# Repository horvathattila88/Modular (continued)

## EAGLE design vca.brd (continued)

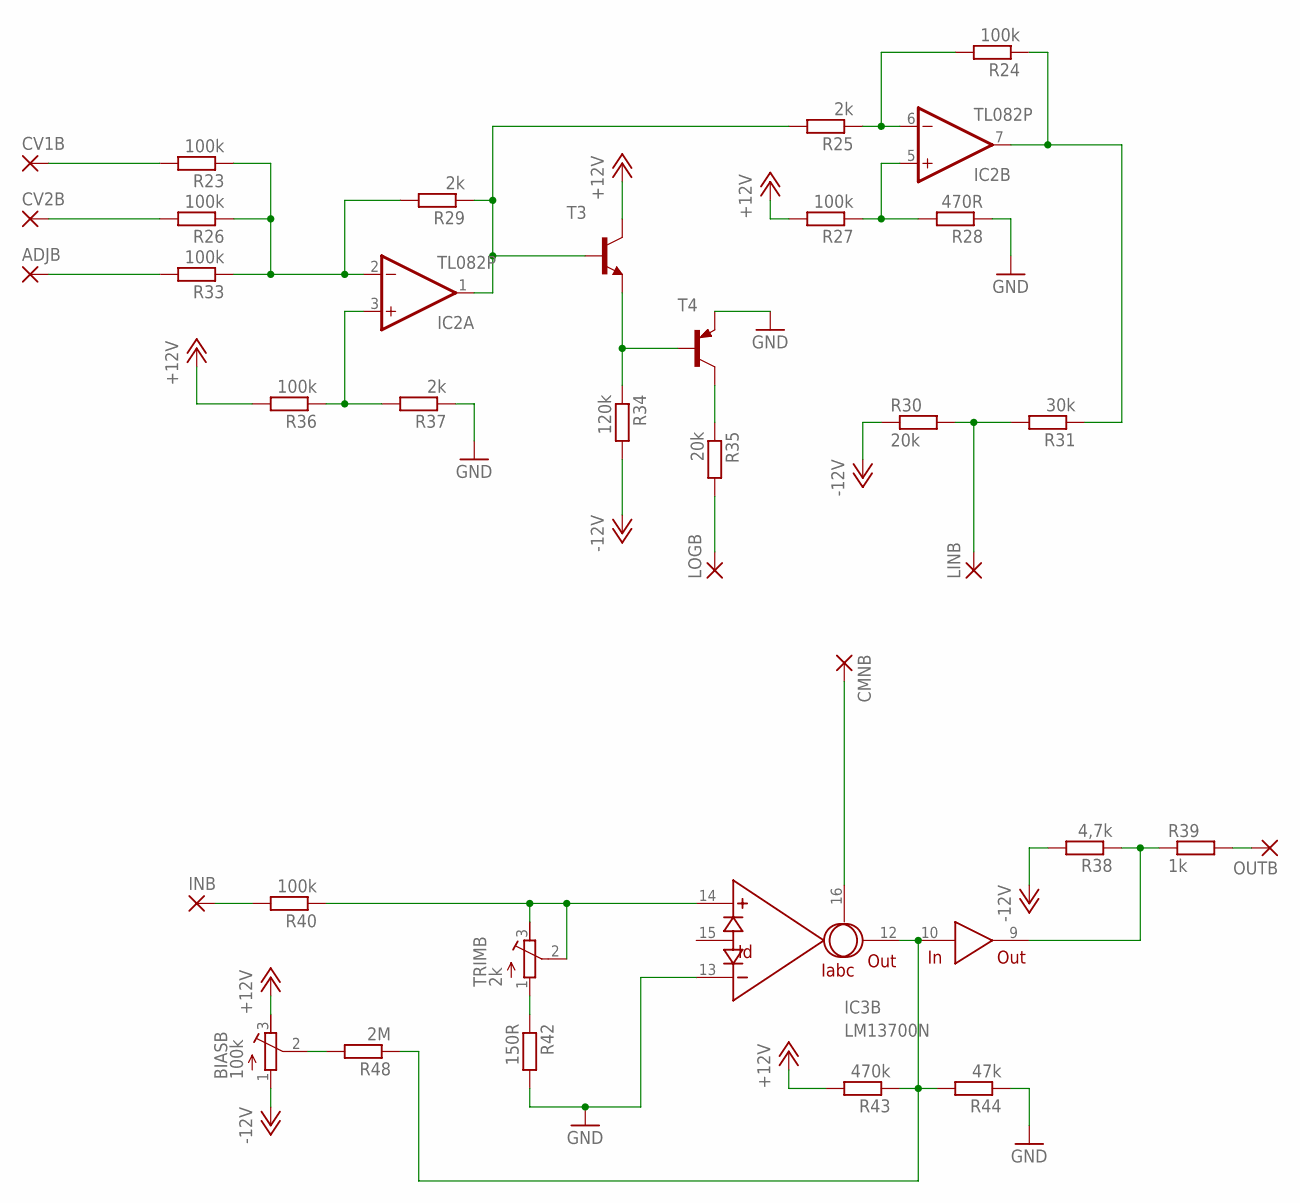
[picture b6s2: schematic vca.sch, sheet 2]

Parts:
ADJB: 2,54/1,0
BIASB: 100k; RTRIM64W
CMNB: 2,54/1,0
CV1B, CV2B: 2,54/1,0
IC2: TL082P; DIL08
IC3: LM13700N; DIL16
INB: 2,54/1,0
LINB: 2,54/1,0
LOGB: 2,54/1,0
OUTB: 2,54/1,0
R23, R26, R33, R40: 100k; 0309V
R24, R27, R36: 100k; 0309/10
R25, R29, R37: 2k; 0309/10
R28: 470R; 0309/10
R30: 20k; 0309V
R31: 30k; 0309V
R34: 120k; 0309/10
R35: 20k; 0309/10
R38: 4,7k; 0309/10
R39: 1k; 0309V
R42: 150R; 0309/10
R43: 470k; 0309/10
R44: 47k; 0309/10
R48: 2M; 0309/10
T3: 2N3904-NPN-TO92-EBC; TO92-EBC
T4: 2N3906-PNP-TO92-EBC; TO92-EBC
TRIMB: 2k; RTRIM64W

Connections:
+12V: BIASB.3 (E), R27.2, R36.2, R43.2, T3.C; also elsewhere on the board
-12V: BIASB.1 (A), R30.1, R34.2, R38.2; also elsewhere on the board
GND: IC3.13 (-IN), R28.1, R37.1, R42.2, R44.1, T4.E; also elsewhere on the board
unnamed: CV1B.1, R23.2
unnamed: CV2B.1, R26.2
unnamed: ADJB.1, R33.2
unnamed: IC2.2 (-IN), R23.1, R26.1, R29.2, R33.1
unnamed: IC2.3 (+IN), R36.1, R37.2
unnamed: IC2.1 (OUT), R25.2, R29.1, T3.B
unnamed: R34.1, T3.E, T4.B
unnamed: R35.1, T4.C
unnamed: LOGB.1, R35.2
unnamed: IC2.6 (-IN), R24.2, R25.1
unnamed: IC2.7 (OUT), R24.1, R31.1
unnamed: IC2.5 (+IN), R27.1, R28.2
unnamed: LINB.1, R30.2, R31.2
unnamed: IC3.10 (IN), IC3.12 (OUT), R43.1, R44.2, R48.1
unnamed: INB.1, R40.2
unnamed: CMNB.1, IC3.16 (IABC)
unnamed: IC3.14 (+IN), R40.1, TRIMB.2 (S), TRIMB.3 (E)
unnamed: R42.1, TRIMB.1 (A)
unnamed: BIASB.2 (S), R48.2
unnamed: OUTB.1, R39.2
unnamed: IC3.9 (OUT), R38.1, R39.1

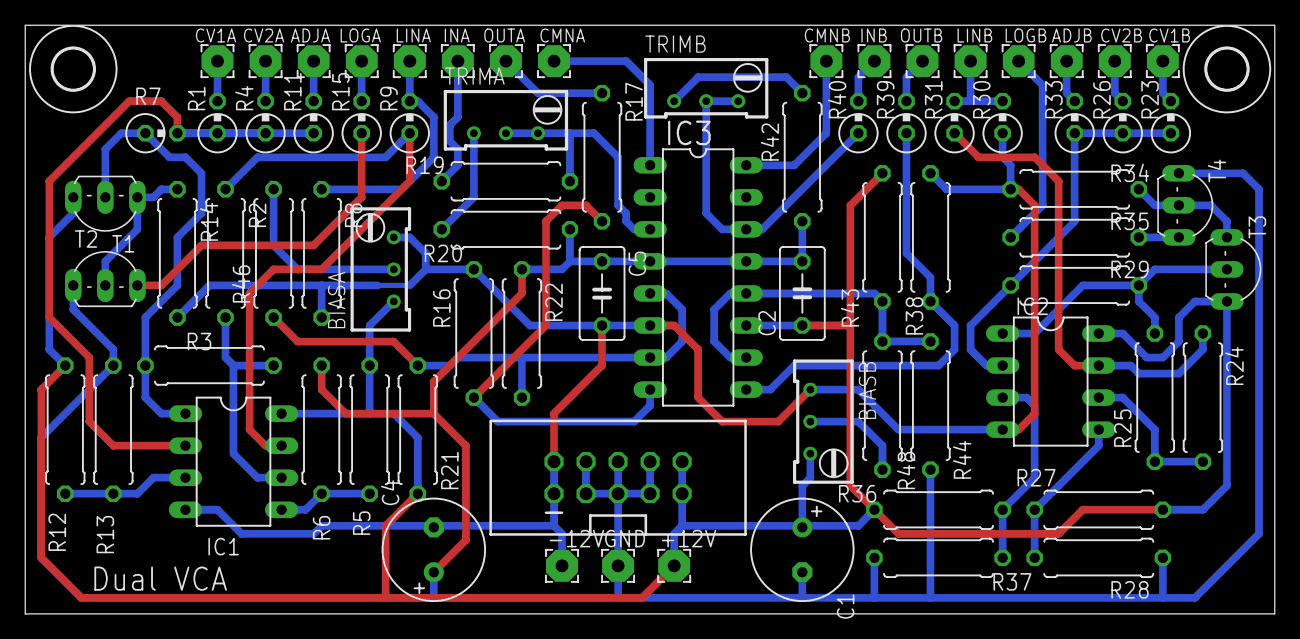
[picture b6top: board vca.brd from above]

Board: 2 copper layers, 99.0 x 46.7 mm, 79 parts (0 on the bottom side), 45 nets.

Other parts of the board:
U$1, U$2: 3,2

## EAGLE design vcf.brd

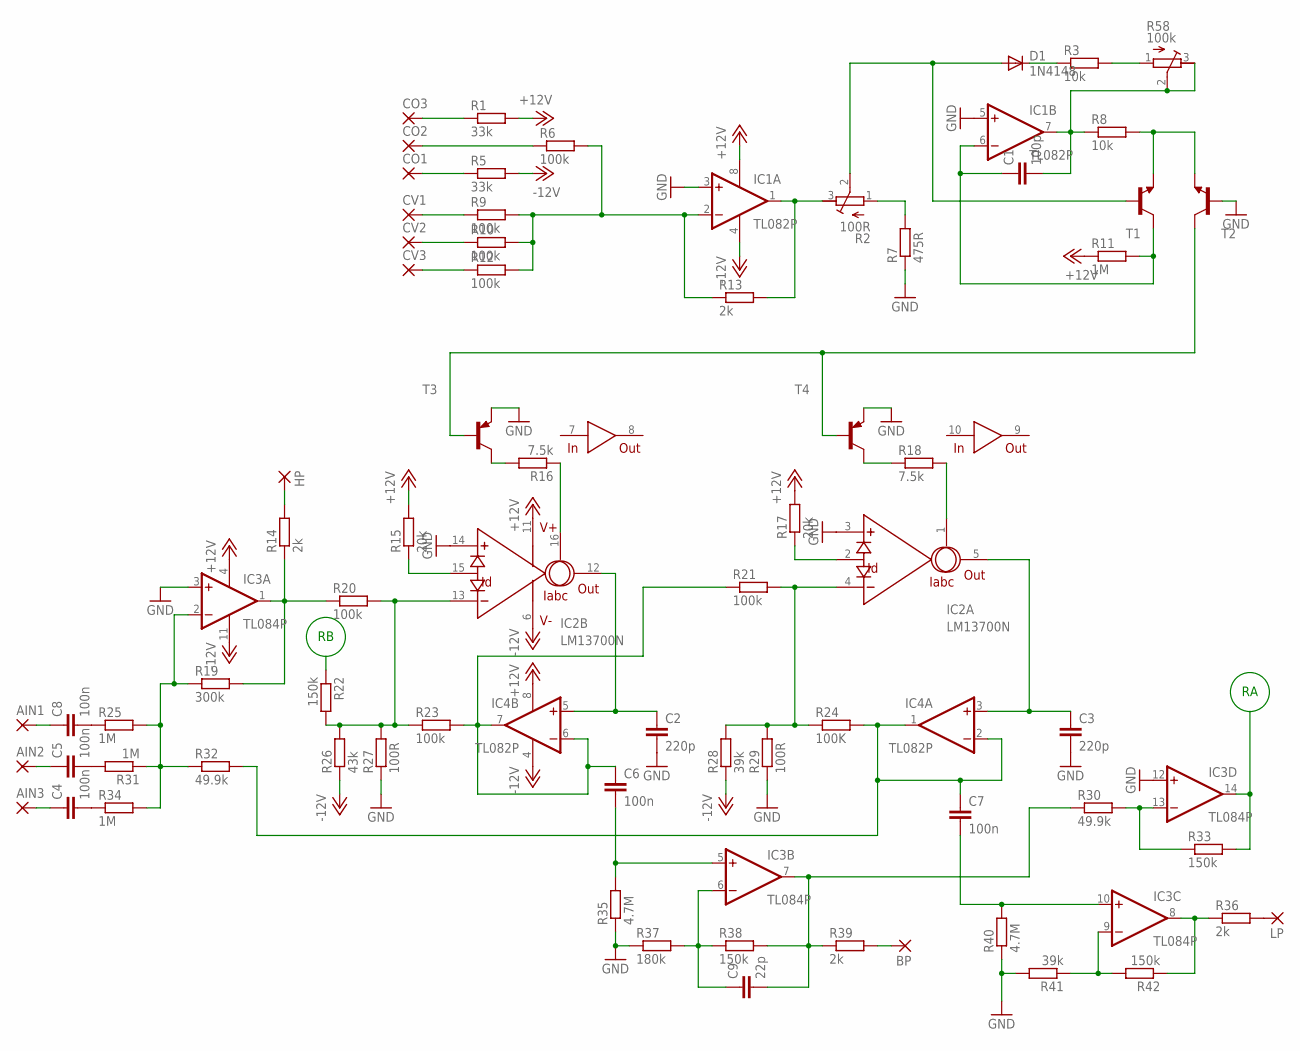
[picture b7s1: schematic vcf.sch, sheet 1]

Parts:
AIN1, AIN2, AIN3: 2,54/1,0
BP: 2,54/1,0
C1: 100p; C050-035X075
C2, C3: 220p; C050-035X075
C4, C5, C6, C7, C8: 100n; C050-035X075
C9: 22p; C050-035X075
CO1, CO2, CO3: 2,54/1,0
CV1, CV2, CV3: 2,54/1,0
D1: 1N4148; DO35-7
HP: 2,54/1,0
IC1, IC4: TL082P; DIL08
IC2: LM13700N; DIL16
IC3: TL084P; DIL14
LP: 2,54/1,0
R1, R5: 33k; 0309V
R2: 100R; RTRIM64W
R3: 10k; 0309V
R6, R9, R10, R12, R20: 100k; 0309V
R7: 475R; 0309V
R8: 10k; 0309/10
R11: 1M; 0309/10
R13, R14: 2k; 0309V
R15, R17: 20k; 0309/10
R16, R18: 7.5k; 0309/10
R19: 300k; 0309V
R21, R23: 100k; 0309/10
R22, R33, R38, R42: 150k; 0309/10
R24: 100K; 0309/10
R25, R31, R34: 1M; 0309V
R26: 43k; 0309V
R27: 100R; 0309V
R28, R41: 39k; 0309/10
R29: 100R; 0309/10
R30: 49.9k; 0309V
R32: 49.9k; 0309/10
R35: 4.7M; 0309V
R36, R39: 2k; 0309/10
R37: 180k; 0309V
R40: 4.7M; 0309/10
R58: 100k; RTRIM64W
T1, T2: 2N3904-NPN-TO92-EBC; TO92-EBC
T3, T4: 2N3906-PNP-TO92-EBC; TO92-EBC

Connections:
+12V: IC1.8 (V+), IC2.11 (V+), IC3.4 (V+), IC4.8 (V+), R1.2, R11.1, R15.2, R17.2; also elsewhere on the board
-12V: IC1.4 (V-), IC2.6 (V-), IC3.11 (V-), IC4.4 (V-), R5.2, R26.1, R28.1; also elsewhere on the board
GND: C2.2, C3.2, IC1.3 (+IN), IC1.5 (+IN), IC2.3 (+IN), IC2.14 (+IN), IC3.3 (+IN), IC3.12 (+IN), R7.1, R27.1, R29.1, R35.1, R37.1, R40.1, R41.2, T2.B, T3.E, T4.E; also elsewhere on the board
unnamed: CO3.1, R1.1
unnamed: CO2.1, R6.1
unnamed: CO1.1, R5.1
unnamed: CV1.1, R9.1
unnamed: CV2.1, R10.1
unnamed: CV3.1, R12.1
unnamed: IC1.2 (-IN), R6.2, R9.2, R10.2, R12.2, R13.1
unnamed: IC1.1 (OUT), R2.3 (E), R13.2
unnamed: R2.1 (A), R7.2
unnamed: C8.2, R25.1
unnamed: R8.2, T1.E, T2.E
unnamed: C1.1, IC1.6 (-IN), R11.2, T1.C
unnamed: D1.C, R3.1
unnamed: R3.2, R58.1 (A)
unnamed: C1.2, IC1.7 (OUT), R8.1, R58.2 (S), R58.3 (E)
unnamed: D1.A, R2.2 (S), T1.B
unnamed: T2.C, T3.B, T4.B
unnamed: C6.2, IC3.5 (+IN), R35.2
unnamed: C5.2, R31.2
unnamed: C4.2, R34.1
unnamed: IC3.1 (OUT), R14.1, R19.2, R20.1
unnamed: HP.1, R14.2
unnamed: IC3.2 (-IN), R19.1, R25.2, R31.1, R32.1, R34.2
unnamed: IC2.13 (-IN), R20.2, R22.2, R23.1, R26.2, R27.2
unnamed: IC2.15 (ID), R15.1
unnamed: IC2.2 (ID), R17.1
unnamed: IC2.16 (IABC), R16.1
unnamed: R16.2, T3.C
unnamed: R18.1, T4.C
unnamed: IC2.1 (IABC), R18.2
unnamed: IC2.4 (-IN), R21.2, R24.1, R28.2, R29.2
unnamed: C6.1, IC4.6 (-IN), IC4.7 (OUT), R21.1, R23.2
unnamed: C2.1, IC2.12 (OUT), IC4.5 (+IN)
unnamed: C3.1, IC2.5 (OUT), IC4.3 (+IN)
unnamed: AIN1.1, C8.1
unnamed: C9.1, IC3.6 (-IN), R37.2, R38.1
unnamed: C9.2, IC3.7 (OUT), R30.1, R38.2, R39.1
unnamed: BP.1, R39.2
unnamed: IC3.13 (-IN), R30.2, R33.1
unnamed: AIN2.1, C5.1
unnamed: C7.2, IC3.10 (+IN), R40.2
unnamed: IC3.9 (-IN), R41.1, R42.2
unnamed: IC3.8 (OUT), R36.1, R42.1
unnamed: LP.1, R36.2
unnamed: AIN3.1, C4.1
unnamed: C7.1, IC4.1 (OUT), IC4.2 (-IN), R24.2, R32.2
RA: IC3.14 (OUT), R33.2; also elsewhere on the board
RB: R22.1; also elsewhere on the board

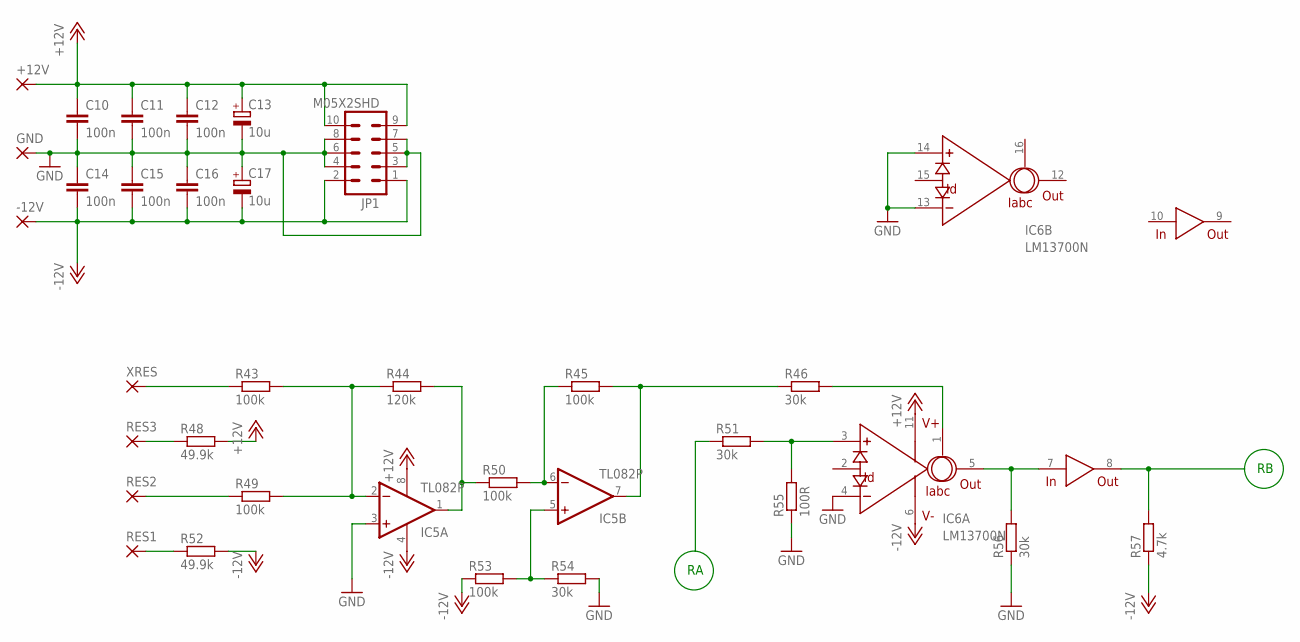
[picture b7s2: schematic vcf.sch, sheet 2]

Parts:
+12V: 2,54/1,0
-12V: 2,54/1,0
C10, C11, C12, C14, C15, C16: 100n; C050-035X075
C13, C17: 10u; E3,5-8
GND: 2,54/1,0
IC5: TL082P; DIL08
IC6: LM13700N; DIL16
JP1: M05X2SHD; 2X5-SHROUDED
R43, R45, R49, R50, R53: 100k; 0309/10
R44: 120k; 0309/10
R46, R51, R54, R56: 30k; 0309/10
R48, R52: 49.9k; 0309/10
R55: 100R; 0309/10
R57: 4.7k; 0309/10
RES1, RES2, RES3: 2,54/1,0
XRES: 2,54/1,0

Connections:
+12V: +12V.1, C10.1, C11.1, C12.1, C13.+, IC5.8 (V+), IC6.11 (V+), JP1.9, JP1.10, R48.2; also elsewhere on the board
-12V: -12V.1, C14.2, C15.2, C16.2, C17.-, IC5.4 (V-), IC6.6 (V-), JP1.1, JP1.2, R52.2, R53.1, R57.1; also elsewhere on the board
GND: C10.2, C11.2, C12.2, C13.-, C14.1, C15.1, C16.1, C17.+, GND.1, IC5.3 (+IN), IC6.4 (-IN), IC6.13 (-IN), IC6.14 (+IN), JP1.3, JP1.4, JP1.5, JP1.6, JP1.7, JP1.8, R54.2, R55.1, R56.1; also elsewhere on the board
unnamed: R43.1, XRES.1
unnamed: R48.1, RES3.1
unnamed: R52.1, RES1.1
unnamed: R49.1, RES2.1
unnamed: IC5.2 (-IN), R43.2, R44.1, R49.2
unnamed: IC5.1 (OUT), R44.2, R50.1
unnamed: IC5.6 (-IN), R45.1, R50.2
unnamed: IC5.5 (+IN), R53.2, R54.1
unnamed: IC6.1 (IABC), R46.2
unnamed: IC5.7 (OUT), R45.2, R46.1
unnamed: IC6.3 (+IN), R51.2, R55.2
unnamed: IC6.5 (OUT), IC6.7 (IN), R56.2
RA: R51.1; also elsewhere on the board
RB: IC6.8 (OUT), R57.2; also elsewhere on the board

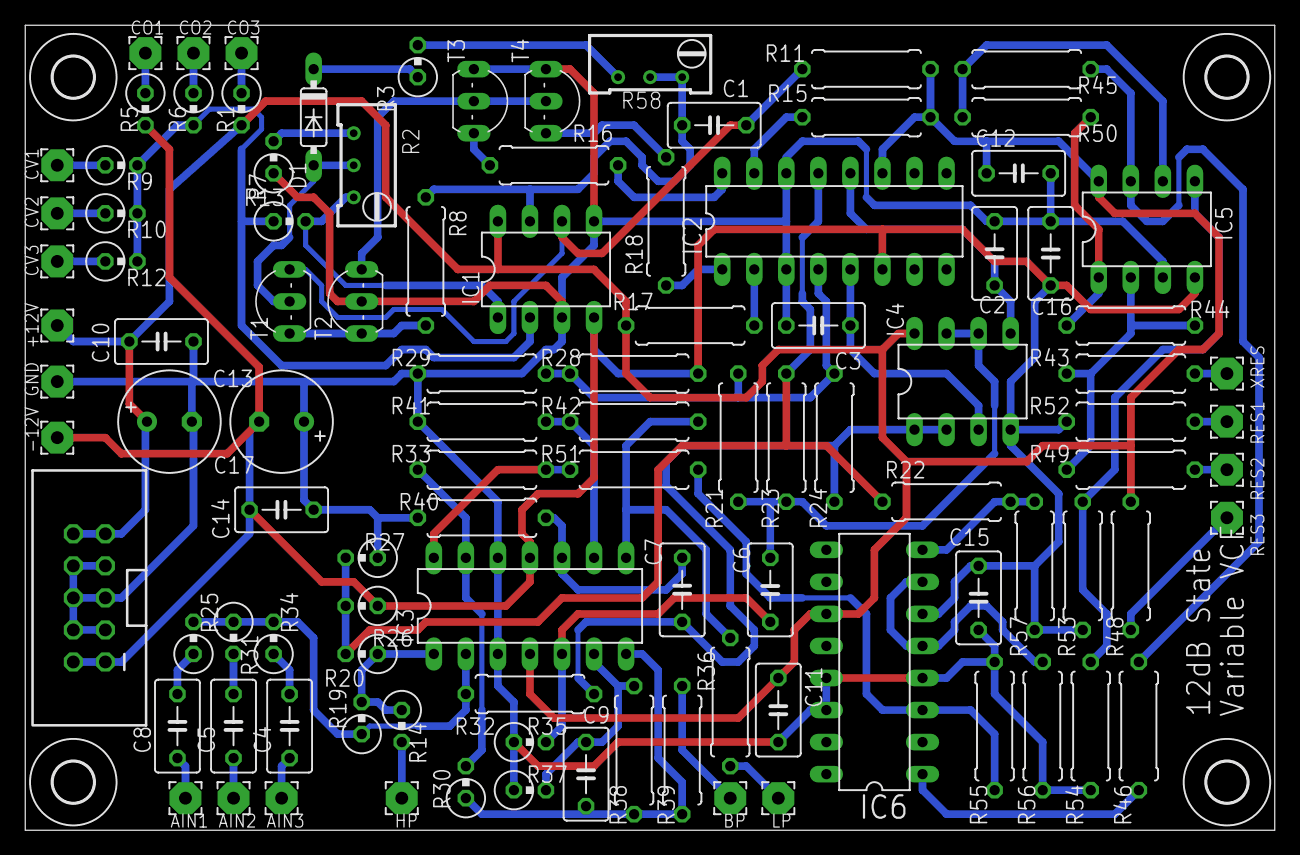
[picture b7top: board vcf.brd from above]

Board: 2 copper layers, 99.0 x 63.8 mm, 108 parts (0 on the bottom side), 63 nets.

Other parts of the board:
U$1, U$2, U$3, U$4: 3,2

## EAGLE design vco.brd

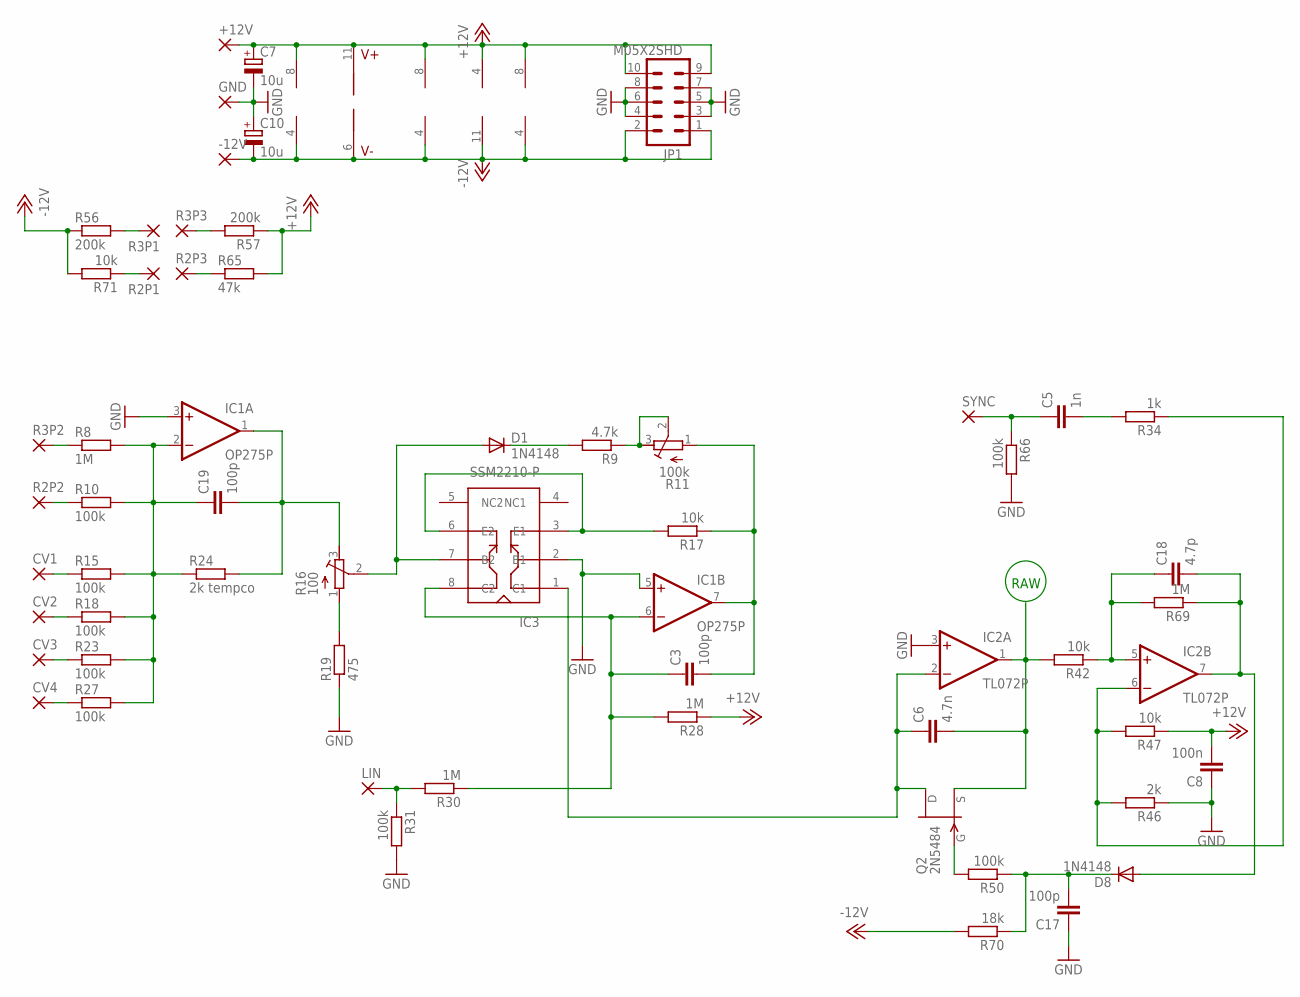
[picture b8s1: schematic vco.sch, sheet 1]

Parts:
+12V: 2,54/1,0
-12V: 2,54/1,0
C3, C17, C19: 100p; C050-045X075
C5: 1n; C050-045X075
C6: 4.7n; C050-045X075
C7, C10: 10u; E2,5-7
C8: 100n; C050-045X075
C18: 4.7p; C050-045X075
CV1, CV2, CV3, CV4: 2,54/1,0
D1, D8: 1N4148; DO35-7
GND: 2,54/1,0
IC1: OP275P; DIL08
IC2, IC6: TL072P; DIL08
IC3: SSM2210-P; DIL08
IC4: TL074P; DIL14
IC5: LM13700N; DIL16
JP1: M05X2SHD; 2X5-SHROUDED
LIN: 2,54/1,0
Q2: 2N5484; TO92-
R2P1, R2P2, R2P3, R3P1, R3P2, R3P3: 2,54/1,0
R8, R28, R30, R69: 1M; 0309V
R9: 4.7k; 0309V
R10, R15, R18, R23, R27, R31, R50, R66: 100k; 0309V
R11: 100k; RTRIM64W
R16: 100; RTRIM64W
R17, R42, R47, R71: 10k; 0309V
R19: 475; 0309V
R24: 2k tempco; 0309/12
R34: 1k; 0309V
R46: 2k; 0309V
R56, R57: 200k; 0309V
R65: 47k; 0309V
R70: 18k; 0309V
SYNC: 2,54/1,0

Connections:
+12V: +12V.1, C7.+, C8.2, IC1.8 (V+), IC2.8 (V+), IC4.4 (V+), IC5.11 (V+), IC6.8 (V+), JP1.9, JP1.10, R28.1, R47.1, R57.1, R65.2; also elsewhere on the board
-12V: -12V.1, C10.-, IC1.4 (V-), IC2.4 (V-), IC4.11 (V-), IC5.6 (V-), IC6.4 (V-), JP1.1, JP1.2, R56.1, R70.2, R71.2; also elsewhere on the board
GND: C7.-, C8.1, C10.+, C17.1, GND.1, IC1.3 (+IN), IC1.5 (+IN), IC2.3 (+IN), IC3.2 (B1), JP1.3, JP1.4, JP1.5, JP1.6, JP1.7, JP1.8, R19.1, R31.2, R46.1, R66.2; also elsewhere on the board
unnamed: R3P1.1, R56.2
unnamed: R2P1.1, R71.1
unnamed: R2P3.1, R65.1
unnamed: R3P3.1, R57.2
unnamed: R3P2.1, R8.1
unnamed: R2P2.1, R10.1
unnamed: CV1.1, R15.1
unnamed: CV2.1, R18.1
unnamed: CV3.1, R23.1
unnamed: CV4.1, R27.1
unnamed: C19.1, IC1.2 (-IN), R8.2, R10.2, R15.2, R18.2, R23.2, R24.1, R27.2
unnamed: C19.2, IC1.1 (OUT), R16.3 (E), R24.2
unnamed: Q2.1 (G), R50.2
unnamed: R16.1 (A), R19.2
unnamed: LIN.1, R30.2, R31.1
unnamed: C3.1, IC1.6 (-IN), IC3.8 (C2), R28.2, R30.1
unnamed: C3.2, IC1.7 (OUT), R11.1 (A), R17.1
unnamed: IC3.3 (E1), IC3.6 (E2), R17.2
unnamed: C17.2, D8.C, R50.1, R70.1
unnamed: C6.1, IC2.2 (-IN), IC3.1 (C1), Q2.3 (D)
unnamed: D1.A, IC3.7 (B2), R16.2 (S)
unnamed: D1.C, R9.2
unnamed: R9.1, R11.2 (S), R11.3 (E)
unnamed: C18.1, IC2.5 (+IN), R42.1, R69.2
unnamed: C18.2, D8.A, IC2.7 (OUT), R69.1
unnamed: IC2.6 (-IN), R34.1, R46.2, R47.2
unnamed: C5.2, R34.2
unnamed: C5.1, R66.1, SYNC.1
RAW: C6.2, IC2.1 (OUT), Q2.2 (S), R42.2; also elsewhere on the board

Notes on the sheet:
RAW

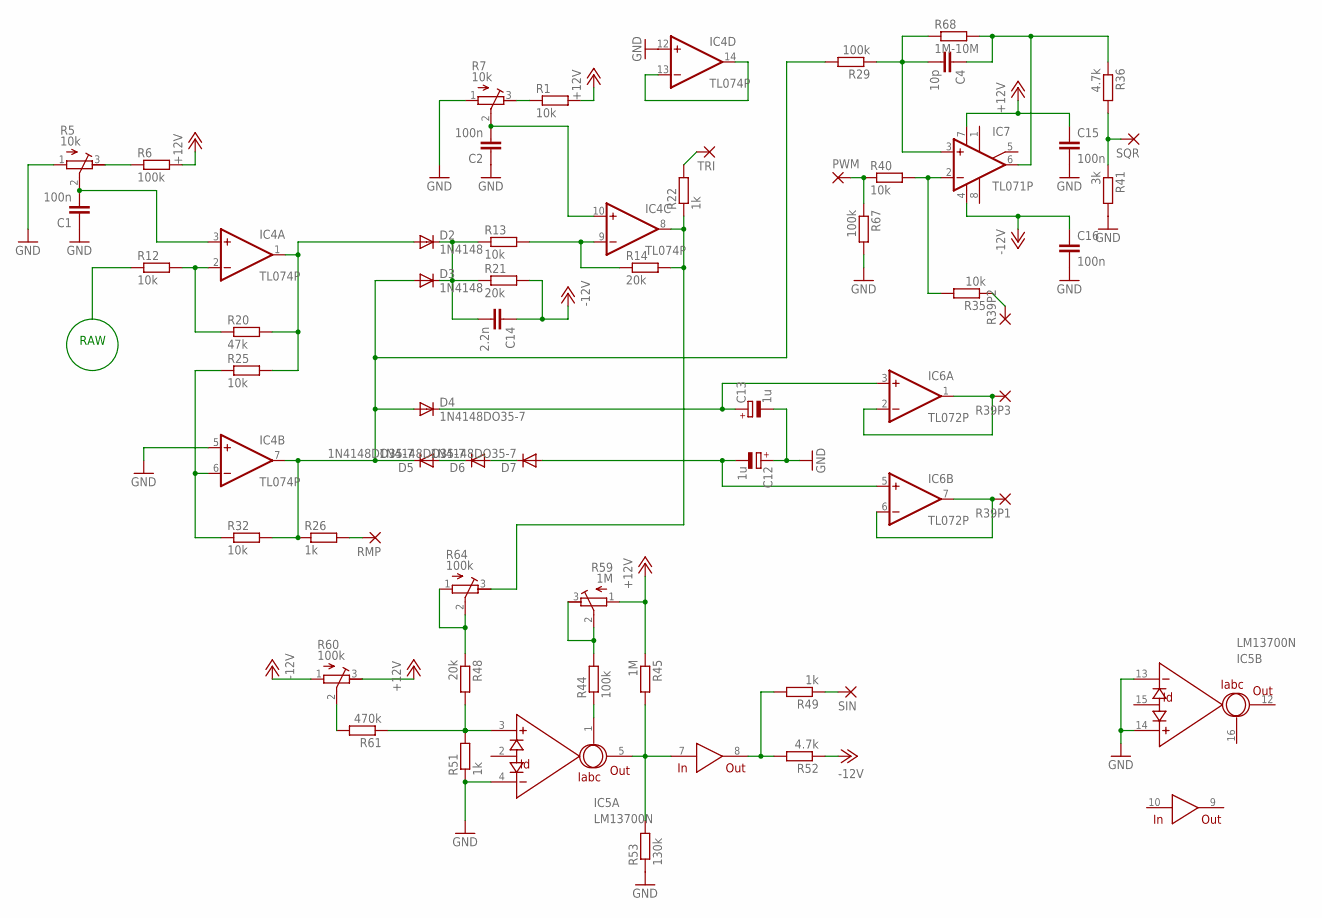
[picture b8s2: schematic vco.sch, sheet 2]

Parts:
C1, C2: 100n; C050-045X075
C4: 10p; C050-045X075
C12, C13: 1u; E2,5-7
C14: 2.2n; C050-045X075
C15, C16: 100n; C050-035X075
D2, D3: 1N4148; DO35-7
D4, D5, D6, D7: 1N4148DO35-7; DO35-7
IC4: TL074P; DIL14
IC5: LM13700N; DIL16
IC6: TL072P; DIL08
IC7: TL071P; DIL08
PWM: 2,54/1,0
R1, R12, R25, R32, R35, R40: 10k; 0309V
R5, R7: 10k; RTRIM64W
R6, R29, R44, R67: 100k; 0309V
R13: 10k; 0309/10
R14, R21, R48: 20k; 0309V
R20: 47k; 0309V
R22, R26, R49, R51: 1k; 0309V
R36, R52: 4.7k; 0309V
R39P1, R39P2, R39P3: 2,54/1,0
R41: 3k; 0309V
R45: 1M; 0309V
R53: 130k; 0309V
R59: 1M; RTRIM64W
R60, R64: 100k; RTRIM64W
R61: 470k; 0309V
R68: 1M-10M; 0309V
RMP: 2,54/1,0
SIN: 2,54/1,0
SQR: 2,54/1,0
TRI: 2,54/1,0

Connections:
+12V: C15.1, IC7.7 (V+), R1.2, R6.2, R45.1, R59.1 (A), R60.3 (E); also elsewhere on the board
-12V: C14.1, C16.1, IC7.4 (V-), R21.2, R52.1, R60.1 (A); also elsewhere on the board
GND: C1.1, C2.1, C12.+, C13.-, C15.2, C16.2, IC4.5 (+IN), IC4.12 (+IN), IC5.4 (-IN), IC5.13 (-IN), IC5.14 (+IN), R5.1 (A), R7.1 (A), R41.2, R51.1, R53.1, R67.2; also elsewhere on the board
unnamed: C2.2, IC4.10 (+IN), R7.2 (S)
unnamed: R1.1, R7.3 (E)
unnamed: R26.2, RMP.1
unnamed: R5.3 (E), R6.1
unnamed: C1.2, IC4.3 (+IN), R5.2 (S)
unnamed: IC4.2 (-IN), R12.2, R20.1
unnamed: D2.A, IC4.1 (OUT), R20.2, R25.2
unnamed: IC4.6 (-IN), R25.1, R32.1
unnamed: IC4.13 (-IN), IC4.14 (OUT)
unnamed: D5.A, D6.C
unnamed: C14.2, D2.C, D3.C, R13.1, R21.1
unnamed: D3.A, D4.A, D5.C, IC4.7 (OUT), R26.1, R29.2, R32.2
unnamed: IC4.9 (-IN), R13.2, R14.1
unnamed: IC4.8 (OUT), R14.2, R22.1, R64.3 (E)
unnamed: R22.2, TRI.1
unnamed: D6.A, D7.C
unnamed: C13.+, D4.C, IC6.3 (+IN)
unnamed: C12.-, D7.A, IC6.5 (+IN)
unnamed: R60.2 (S), R61.2
unnamed: R35.1, R39P2.1
unnamed: R36.2, R41.1, SQR.1
unnamed: IC7.2 (-IN), R35.2, R40.2
unnamed: PWM.1, R40.1, R67.1
unnamed: C4.2, IC7.3 (+IN), R29.1, R68.1
unnamed: C4.1, IC7.6 (OUT), R36.1, R68.2
unnamed: IC5.3 (+IN), R48.2, R51.2, R61.1
unnamed: R48.1, R64.1 (A), R64.2 (S)
unnamed: IC6.1 (OUT), IC6.2 (-IN), R39P3.1
unnamed: IC6.6 (-IN), IC6.7 (OUT), R39P1.1
unnamed: IC5.5 (OUT), IC5.7 (IN), R45.2, R53.2
unnamed: IC5.1 (IABC), R44.1
unnamed: IC5.8 (OUT), R49.2, R52.2
unnamed: R44.2, R59.2 (S), R59.3 (E)
unnamed: R49.1, SIN.1
RAW: R12.1; also elsewhere on the board

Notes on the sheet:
RAW

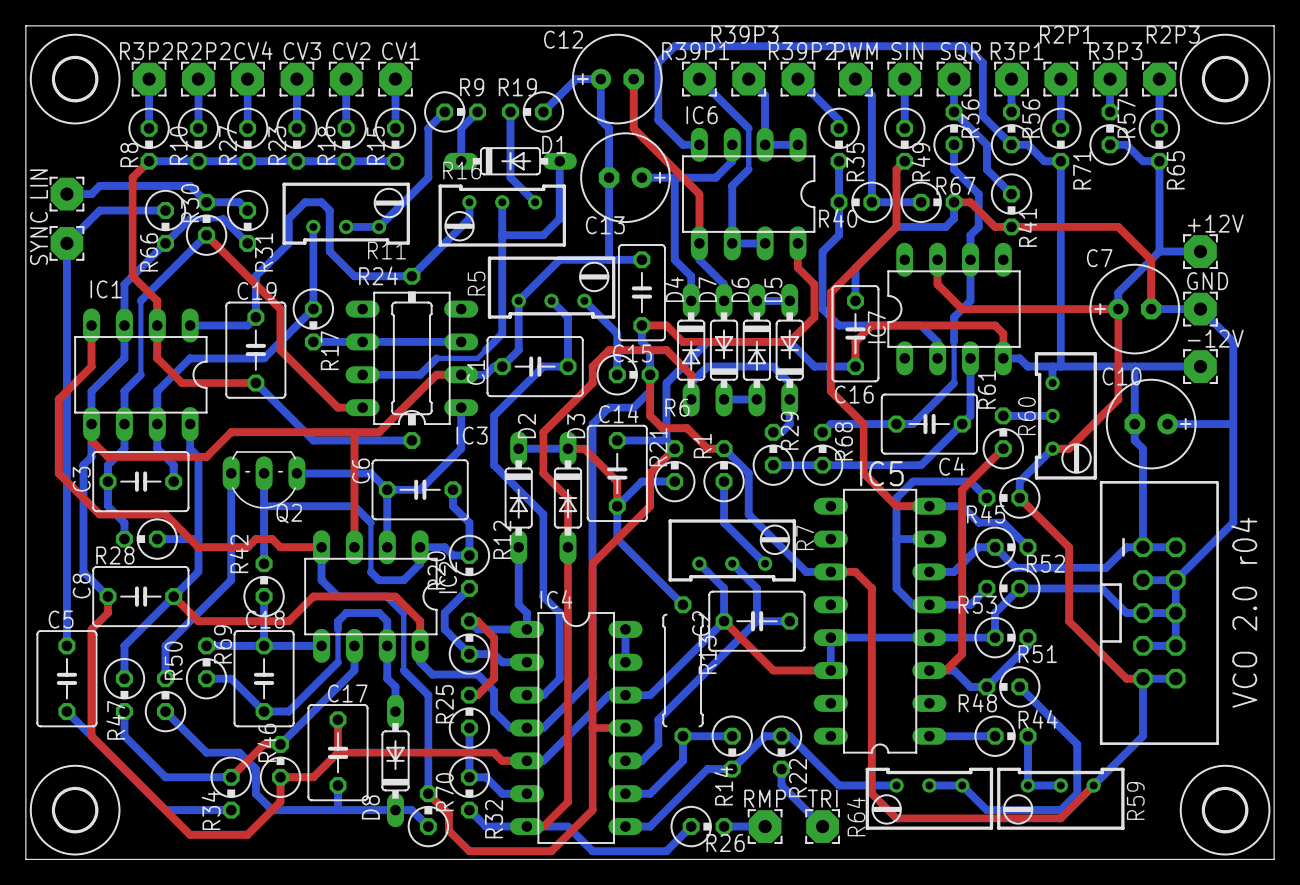
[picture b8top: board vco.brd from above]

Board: 2 copper layers, 96.5 x 64.4 mm, 119 parts (0 on the bottom side), 66 nets.

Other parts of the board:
U$1, U$2, U$3, U$4: 3,2
